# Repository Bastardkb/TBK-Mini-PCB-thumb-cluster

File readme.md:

# TBK Mini PCB - thumbs

Flexible PCB made for the TBK Mini and Skeletyl.

With per-key RGB.

This repository contains all files necessary to order a PCB.

If you want to modify the design files, the Kicad sources are included.
If you just want to order the PCBs, check out the Release section which contain the gerber files.

## How to order

Order with a 0.6mm or 0.8mm PCB thickness

## License

Licensed under CC BY-NC-SA 4.0
Copyright Quentin Lebastard 2021

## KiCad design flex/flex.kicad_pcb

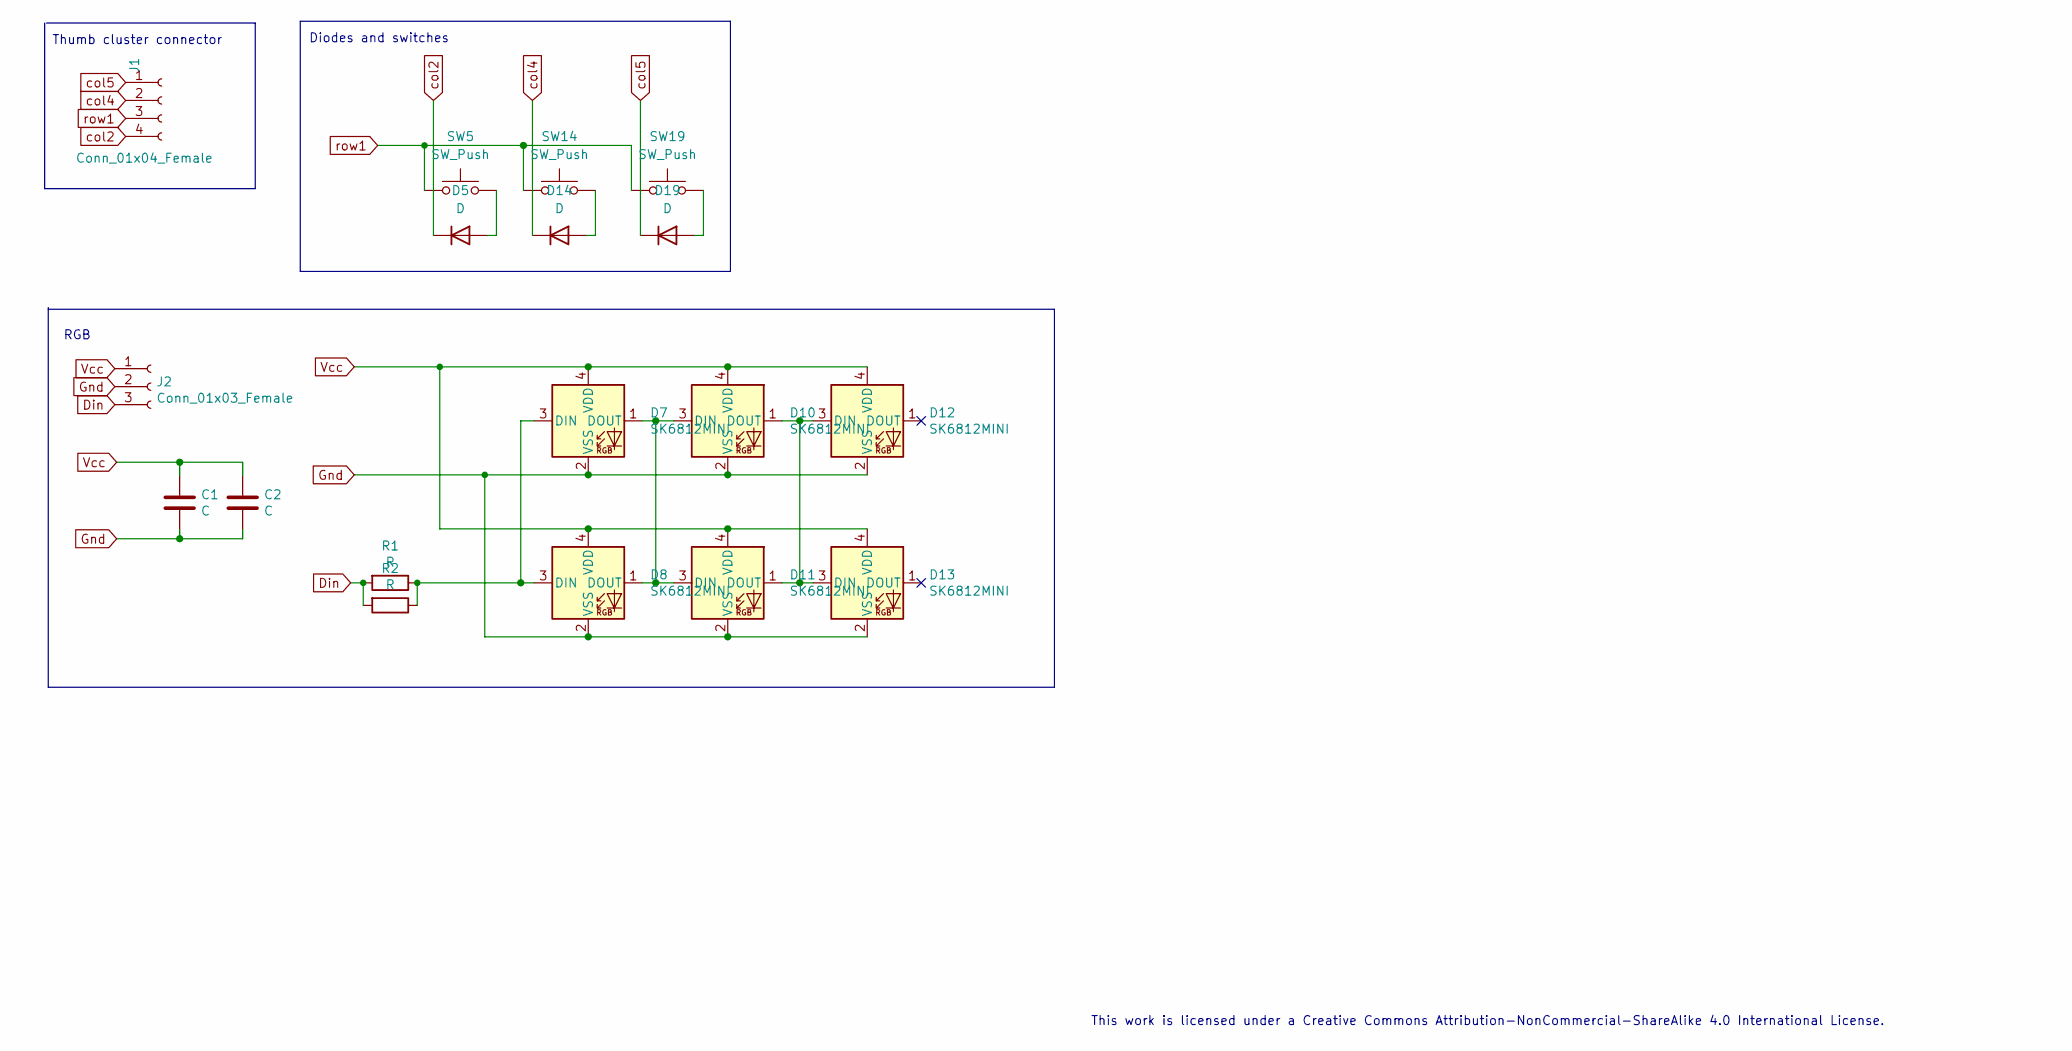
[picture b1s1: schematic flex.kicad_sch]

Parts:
C1, C2: C; LED_1206_3216Metric_Pad1.42x1.75mm_HandSolder
D5, D14, D19: D; Diode_TH_SOD123
D7, D10, D12: SK6812MINI; YS-SK6812MINI-E_REVERSE
D8, D11, D13: SK6812MINI; YS-SK6812MINI-E_REVERSE_NO_EDGECUT
J1: Conn_01x04_Female; PinHeader_1x04_P2.54mm_Vertical
J2: Conn_01x03_Female; PinHeader_1x03_P2.54mm_Vertical
R1, R2: R; R_1206_3216Metric_Pad1.42x1.75mm_HandSolder
SW5, SW14, SW19: SW_Push; SW_MX_reversible

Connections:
Din: J2.3, R1.2, R2.2
Gnd: C1.2, C2.2, D7.2 (VSS), D8.2 (VSS), D10.2 (VSS), D11.2 (VSS), D12.2 (VSS), D13.2 (VSS), J2.2
unnamed: D5.2 (A), SW5.2
unnamed: D7.3 (DIN), D8.3 (DIN), R1.1, R2.1
unnamed: D10.1 (DOUT), D11.1 (DOUT), D12.3 (DIN), D13.3 (DIN)
unnamed: D7.1 (DOUT), D8.1 (DOUT), D10.3 (DIN), D11.3 (DIN)
unnamed: D14.2 (A), SW14.2
unnamed: D19.2 (A), SW19.2
Vcc: C1.1, C2.1, D7.4 (VDD), D8.4 (VDD), D10.4 (VDD), D11.4 (VDD), D12.4 (VDD), D13.4 (VDD), J2.1
col2: D5.1 (K), J1.4
col4: D14.1 (K), J1.2
col5: D19.1 (K), J1.1
row1: J1.3, SW5.1, SW14.1, SW19.1

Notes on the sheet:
Diodes and switches
This work is licensed under a Creative Commons Attribution-NonCommercial-ShareAlike 4.0 International License.
RGB
Thumb cluster connector

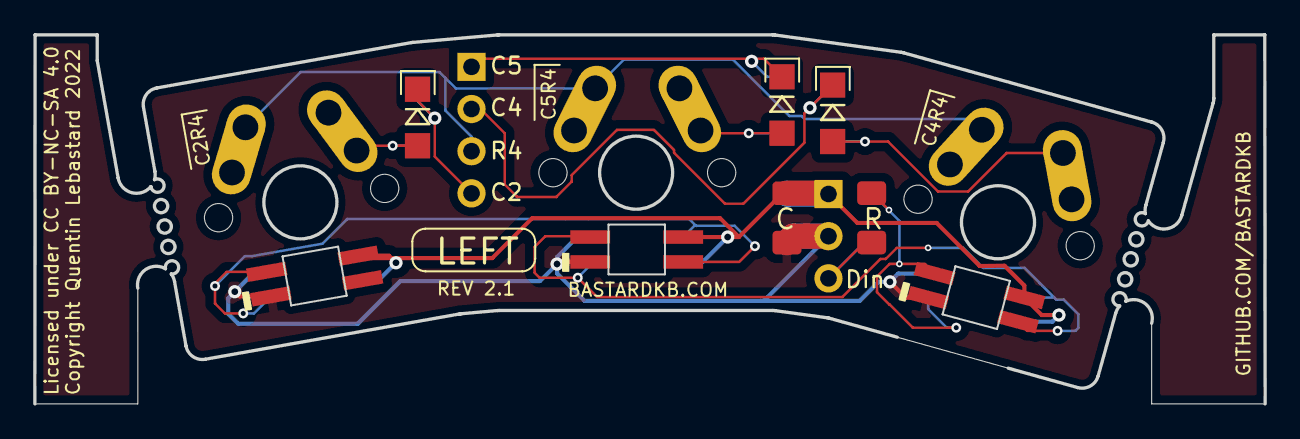
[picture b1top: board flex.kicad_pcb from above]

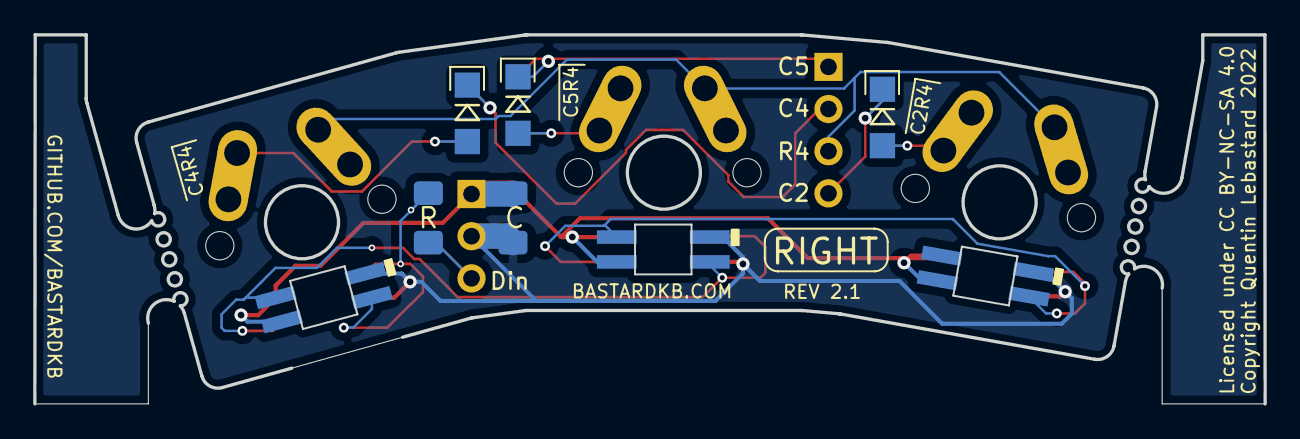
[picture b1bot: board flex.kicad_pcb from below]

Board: 2 copper layers, 74.1 x 22.2 mm, 18 parts (5 on the bottom side), 13 nets.

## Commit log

2022-01-14 files
2022-01-19 add pic
2022-01-24 bork

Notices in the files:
flex/flex.kicad_pcb:
Copyright Quentin Lebastard 2022
